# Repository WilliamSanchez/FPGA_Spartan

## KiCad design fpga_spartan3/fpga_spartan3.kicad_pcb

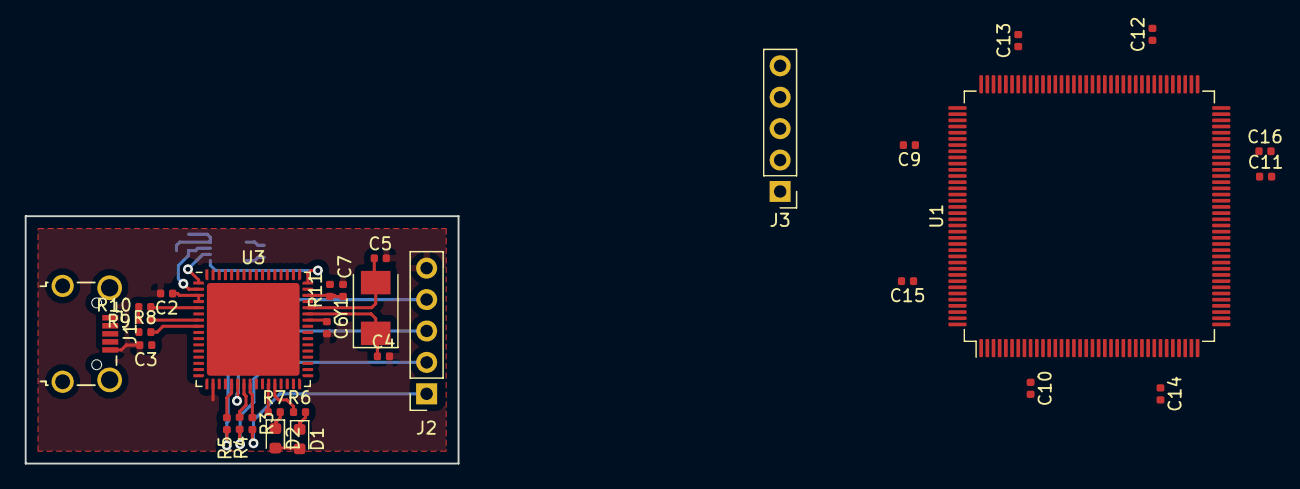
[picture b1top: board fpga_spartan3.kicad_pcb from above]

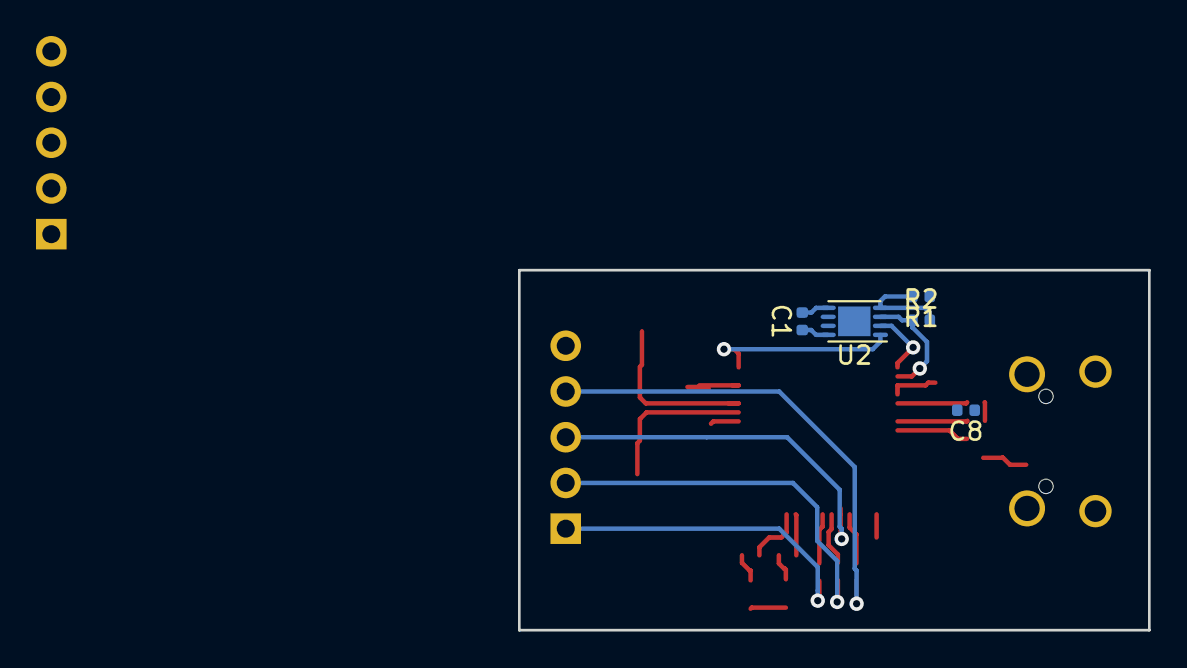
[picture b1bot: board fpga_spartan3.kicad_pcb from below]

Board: 2 copper layers, 35.0 x 20.0 mm, 36 parts (5 on the bottom side), 33 nets.

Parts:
C1, C2, C3, C6, C7, C8, C13, C14, C15, C16: 0.1uF; C_0402_1005Metric
C4, C5: 27pF; C_0402_1005Metric
C9, C10, C11, C12: 0,1uF; C_0402_1005Metric
D1: BLUE; LED_0603_1608Metric
D2: GREEN; LED_0603_1608Metric
J1: USB_B_Mini; USB_Micro-B_Wuerth_629105150521_CircularHoles
J2: JTAG; PinSocket_1x05_P2.54mm_Vertical
J3: Conn_JTAG; PinHeader_1x05_P2.54mm_Vertical
R1: 10K; R_0402_1005Metric
R2: 2.2K; R_0402_1005Metric
R3, R4, R5: 68; R_0402_1005Metric
R6, R7: 220; R_0402_1005Metric
R8, R9: 27; R_0402_1005Metric
R10: 1.5K; R_0402_1005Metric
R11: 470; R_0402_1005Metric
U1: XC3S250E-4TQG144C; TQFP-144_20x20mm_P0.5mm
U2: 93LCxxB; TDFN-8-1EP_3x2mm_P0.5mm_EP1.80x1.65mm
U3: FT2232D; QFN-64-1EP_9x9mm_P0.5mm_EP7.5x7.5mm
Y1: 6MHz; Crystal_SMD_Abracon_ABM3-2Pin_5.0x3.2mm

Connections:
+1V2: C9.1, C10.1, C11.1, C12.1, U1.9, U1.45, U1.80, U1.115
+2V5: U1.13, U1.28, U1.42, U1.49, U1.64, U1.79, U1.100, U1.121, U1.138
+3V3: C13.1, C14.1, C15.1, C16.1, D1.2, D2.2, U1.30, U1.65, U1.102, U1.137, U3.10, U3.14, U3.26, U3.31
+5V: C1.1, C2.1, C3.1, C6.1, J1.1, R1.1, R11.2, U2.8, U3.3, U3.4, U3.42
/program/AVCC: C7.1, R11.1, U3.46
/program/CS: U2.1, U3.48
/program/TCK: J2.1, R3.2
/program/TDI: J2.2, R4.2
/program/TDO: J2.3, U3.22
/program/TMS: J2.4, R5.2
GND: C1.2, C2.2, C3.2, C4.2, C5.2, C6.2, C7.2, C8.1, C9.2, C10.2, C11.2, C12.2, C13.2, C14.2, C15.2, C16.2, J1.5, J2.5, J3.5, U1.11, U1.19, U1.27, U1.37, U1.46, U1.55, U1.61, U1.73, U1.90, U1.99, U1.118, U1.127, U1.133, U2.5, U3.9, U3.18, U3.25, U3.34, U3.45, U3.47
unnamed: C4.1, U3.43, Y1.1
unnamed: C5.1, U3.44, Y1.2
unnamed: C8.2, U3.6
unnamed: D1.1, R6.2
unnamed: D2.1, R7.2
unnamed: J1.2, R9.1, R10.1
unnamed: J1.3, R8.1
unnamed: J3.1, U1.110
unnamed: J3.2, U1.108
unnamed: J3.3, U1.144
unnamed: J3.4, U1.109
unnamed: R1.2, R2.2, U2.4
unnamed: R2.1, U2.3, U3.2
unnamed: R3.1, U3.24
unnamed: R4.1, U3.23
unnamed: R5.1, U3.21
unnamed: R6.1, U3.28
unnamed: R7.1, U3.27
unnamed: R8.2, U3.8
unnamed: R9.2, U3.7
unnamed: R10.2, U3.5
unnamed: U2.2, U3.1

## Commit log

2021-04-02 Initialzation
